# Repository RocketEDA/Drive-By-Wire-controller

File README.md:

# DBW-controller

DISCLAIMER: Please read the LICENSE file. Electronic throttle body control is not for the faint of heart. It can result in injury or death of road users. Test, verify, and test again before using on a road with other people. Understand the software and hardware, how they interact, apply good engineering principles and common sense.
As stated in the LICENSE file, by using this project in any way, you agree to take on full responsibilities to damages caused by this project.

Drive by wire controller, maps throttle to throttle body 1:1 with idle control

For my application I used a Chrysler/mercedes 75mm throttle body with a corvette c6 throttle pedal.
P/N 0280750570
P/N 25835421

SOFTWARE:
Code is fully commented.

Schematic description:
arduino nano handles all the code and control. 
D2 has an input for switch SW2, signaling to enter setup mode
A6 has a potentiometer, handling idle control.
For servo drive a BTS7960 module from amazon is used.

PCA9685 is used for better PWM control. PWM0 and PWM is used for the BTS, the rest are open

Optionally popuplate R11 and R12. The chrylser TB used a HAR3726 magnetic sensor which specifies for a 10k RL

Assembly notes:
The capacitor and terminal blocks will need to moved to the other side on the BTS7960 to clear. I took this opportunity to upsize the capacitor as well, not sure if there's any appreciatable benefit.

J2 and J4 connect to the TB TPS and e-pedal TPS.
Both e-pedal TPS's are positive direction, aka voltage increases as TPS approaches "open"
TB TPS has one signal inverted. To change this the calculation can be modified:

Upon first run, the "setup" switch should be set. Plugin a USB and set baud to 115200 to follow setup instructions. The potentiometer sets idle (minimum) throttle position. The equation is as follows. Insert a DMM probe between GND and IDLE to measure the pot's voltage. The idle % equation is: Idle position % = (IDLE voltage / 5) * (MAX_IDLE_TB_OPEN / 1023) * 100

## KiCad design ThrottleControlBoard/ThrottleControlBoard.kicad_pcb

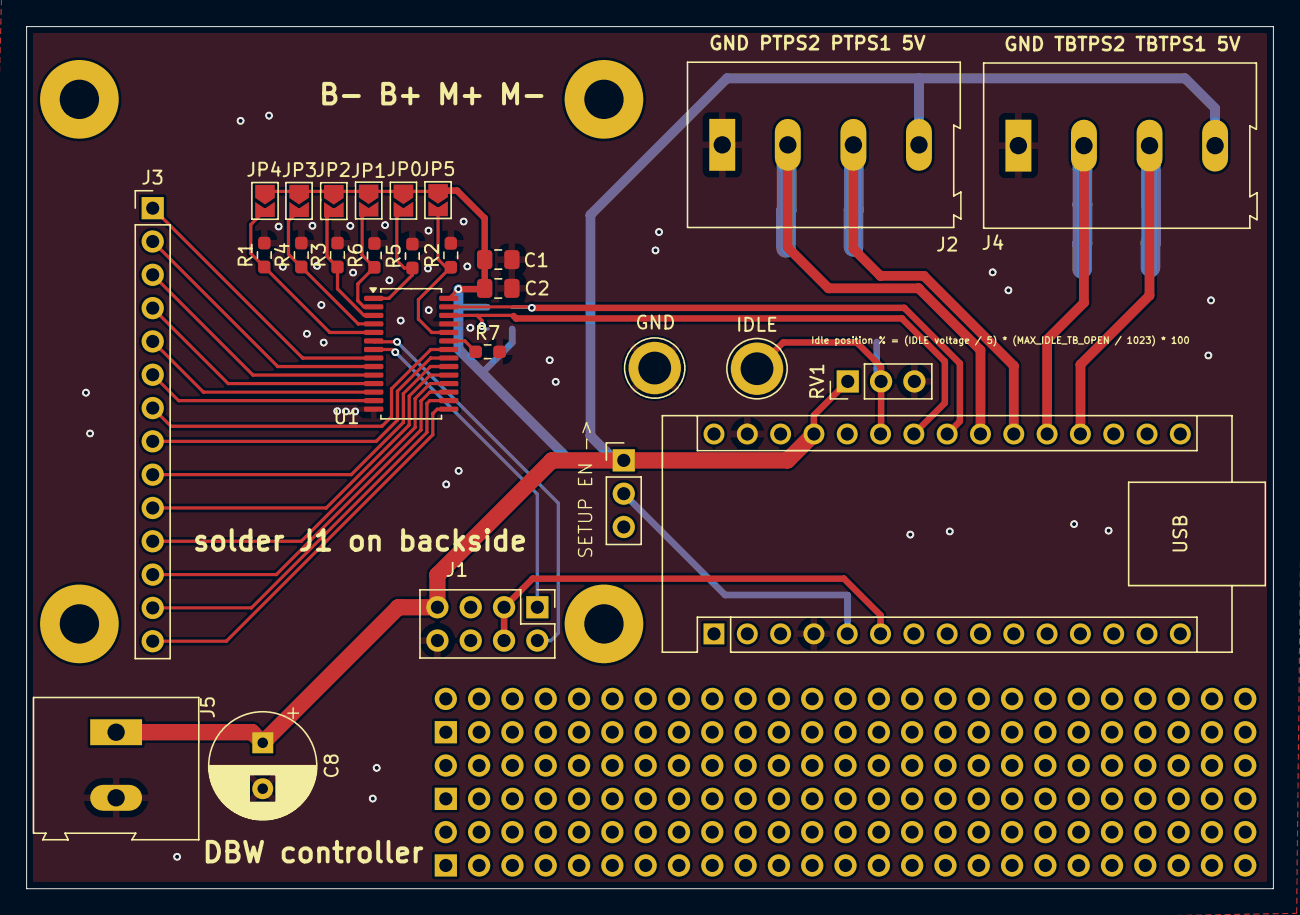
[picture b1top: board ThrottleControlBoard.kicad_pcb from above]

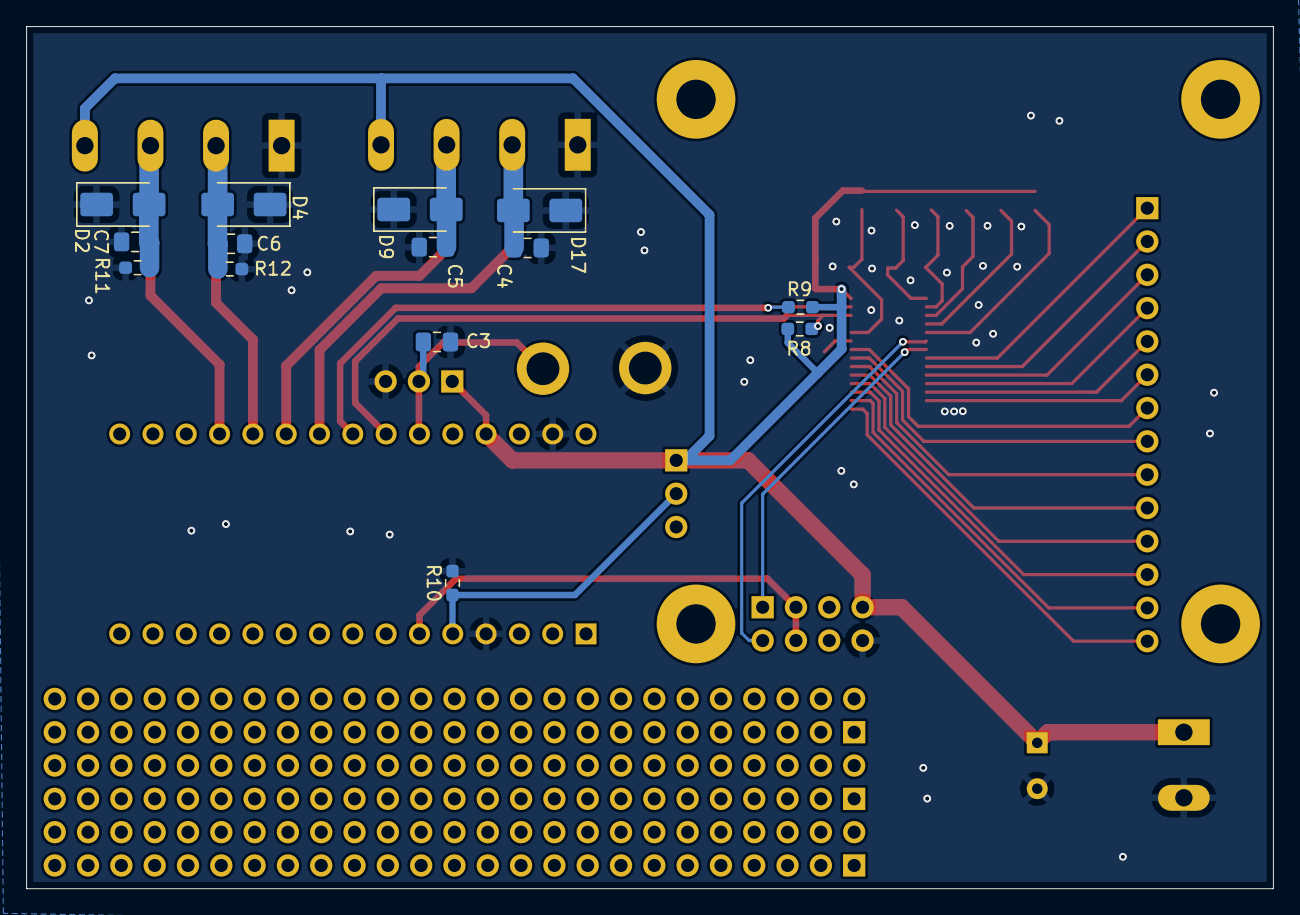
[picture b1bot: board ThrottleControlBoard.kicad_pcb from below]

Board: 2 copper layers, 95.1 x 65.7 mm, 44 parts (14 on the bottom side), 34 nets.

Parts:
A1: Arduino_Nano_Every; Arduino_Nano
C1: 10uF; C_0805_2012Metric_Pad1.18x1.45mm_HandSolder
C2: 100nF; C_0805_2012Metric_Pad1.18x1.45mm_HandSolder
C3, C4, C5, C6, C7: 1nF; C_0805_2012Metric_Pad1.18x1.45mm_HandSolder
C8: 470uF; CP_Radial_D8.0mm_P3.50mm
D2, D4, D9, D17: SMAJ5.0CA; D_SMA
J1: BTS7960 module; PinHeader_2x04_P2.54mm_Vertical
J2: e-Throttle; TerminalBlock_Altech_AK300-4_P5.00mm
J3: Conn_01x14; PinHeader_1x14_P2.54mm_Vertical
J4: TB TPS; TerminalBlock_Altech_AK300-4_P5.00mm
J5: 5V; TerminalBlock_Altech_AK300-2_P5.00mm
J6, J7, J10: Conn_02x25_Odd_Even; PinHeader_2x25_P2.54mm_Vertical
JP0, JP1, JP2, JP3, JP4, JP5: SolderJumper_2_Open; SolderJumper-2_P1.3mm_Open_TrianglePad1.0x1.5mm
R1, R2, R3, R4, R5, R6, R7, R8, R9, R10, R11, R12: 10k; R_0603_1608Metric_Pad0.98x0.95mm_HandSolder
RV1: R_Potentiometer_Trim; PinHeader_1x03_P2.54mm_Vertical
SW2: SW_SPDT; PinHeader_1x03_P2.54mm_Vertical
TP1: IDLE; TestPoint_Loop_D3.80mm_Drill2.5mm
TP2: GND; TestPoint_Loop_D3.80mm_Drill2.5mm
U1: PCA9685PW; TSSOP-28_4.4x9.7mm_P0.65mm

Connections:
GND: A1.4 (GND), A1.29 (GND), C1.2, C2.2, C3.2, C4.2, C5.2, C6.2, C7.2, C8.2, D2.1 (A1), D4.1 (A1), D9.1 (A1), D17.1 (A1), J1.8, J2.1, J4.1, J5.2, R1.2, R2.2, R3.2, R4.2, R5.2, R6.2, R7.2, R10.2, R11.2, R12.2, RV1.3, TP2.1, U1.14 (VSS), U1.25 (EXTCLK)
L_EN: A1.6 (D3), J1.3, J1.4
L_PWM: J1.2, U1.6 (LED0)
unnamed: A1.25 (A6), C3.1, RV1.2, TP1.1
unnamed: A1.5 (D2), R10.1, SW2.2 (B)
unnamed: JP0.2 (B), R5.1, U1.1 (A0)
unnamed: JP1.2 (B), R6.1, U1.2 (A1)
unnamed: JP2.2 (B), R3.1, U1.3 (A2)
unnamed: JP3.2 (B), R4.1, U1.4 (A3)
unnamed: JP4.2 (B), R1.1, U1.5 (A4)
unnamed: JP5.2 (B), R2.1, U1.24 (A5)
unnamed: R7.1, U1.23 (~OE)
PTPS1: A1.21 (A2), C5.1, D9.2 (A2), J2.3
PTPS2: A1.22 (A3), C4.1, D17.2 (A2), J2.2
PWM1: J1.1, U1.7 (LED1)
PWM2: J3.1, U1.8 (LED2)
PWM3: J3.2, U1.9 (LED3)
PWM4: J3.3, U1.10 (LED4)
PWM5: J3.4, U1.11 (LED5)
PWM6: J3.5, U1.12 (LED6)
PWM7: J3.6, U1.13 (LED7)
PWM8: J3.14, U1.15 (LED8)
PWM9: J3.13, U1.16 (LED9)
PWM10: J3.12, U1.17 (LED10)
PWM11: J3.11, U1.18 (LED11)
PWM12: J3.10, U1.19 (LED12)
PWM13: J3.9, U1.20 (LED13)
PWM14: J3.8, U1.21 (LED14)
PWM15: J3.7, U1.22 (LED15)
SCL: A1.24 (SCL/A5), R8.2, U1.26 (SCL)
SDA: A1.23 (SDA/A4), R9.2, U1.27 (SDA)
TBTPS1: A1.19 (A0), C7.1, D2.2 (A2), J4.3, R11.1
TBTPS2: A1.20 (A1), C6.1, D4.2 (A2), J4.2, R12.1
VDD: A1.27 (+5V), C1.1, C2.1, C8.1, J1.7, J2.4, J4.4, J5.1, JP0.1 (A), JP1.1 (A), JP2.1 (A), JP3.1 (A), JP4.1 (A), JP5.1 (A), R8.1, R9.1, RV1.1, SW2.1 (A), U1.28 (VDD)

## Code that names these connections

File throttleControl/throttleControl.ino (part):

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//PCA9685 pins
#define LPWM_pin 0      //PWM pin on PCA9685
#define RPWM_pin 1      //PWM pin on PCA9685
#define EN_pin 3        //R_EN/L_EN tied together
//#define RIS_pin         //overcurrent alarm right
//#define LIS_pin         //overcurrent alarm right

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#define PTPS_var 300

//throttle body pot pins
#define TBTPS1_pin A0
#define TBTPS2_pin A1

//e-pedal pot pins
#define PTPS1_pin A2
#define PTPS2_pin A3

//min throttle idle pot pin
#define IDLE_POT_pin A6
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*/
void readTBTPS()
{
  tbtps1_val = analogRead(TBTPS1_pin);
  tbtps2_val = analogRead(TBTPS2_pin);
}

/*
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void readPTPS()
{
  //invert if pins are inversed
  ptps1_val = analogRead(PTPS2_pin);
  ptps2_val = analogRead(PTPS1_pin);
}
/*
   calculateTBTPS
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
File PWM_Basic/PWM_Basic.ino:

/****************************************************************************************************************************
  PWM_Basic.ino

  For AVR-based boards  (UNO, Nano, Mega, 32U4, 16U4, etc. )
  Written by Khoi Hoang

  Built by Khoi Hoang https://github.com/khoih-prog/AVR_PWM
  Licensed under MIT license

  This is pure hardware-based PWM
*****************************************************************************************************************************/
/******************************************************************************************************************************
  // For UNO / Nano
  Timer0 ( 8-bit) used by delay(), millis() and micros(), and PWM generation on pins 5 (6 not usable)
  Timer1 (16-bit) used by the Servo.h library and PWM generation on pins 9 and 10
  Timer2 ( 8-bit) used by Tone() and PWM generation on pins 3 and 11
  // For Mega
  Timer0 ( 8-bit) used by delay(), millis() and micros(), and PWM generation on pins 4 (13 not usable)
  Timer1 (16-bit) used by the Servo.h library and PWM generation on pins 11, 12
  Timer2 ( 8-bit) used by Tone() and PWM generation on pins 9 and 10
  Timer3 (16-bit) used by PWM generation on pins  2,  3 and  5
  Timer4 (16-bit) used by PWM generation on pins  6,  7 and  8
  Timer5 (16-bit) used by PWM generation on pins 44, 45 and 46

  ////////////////////////////////////////////
  // For Mega (2, 3, 4, 5, 6, 7, 8, 9, 10, 11, 12, 13, 44, 45, 46)
  Pin  2 => TIMER3B   // PE 4 ** 2  ** PWM2
  Pin  3 => TIMER3C   // PE 5 ** 3  ** PWM3
  Pin  4 => TIMER0B   // PG 5 ** 4  ** PWM4
  Pin  5 => TIMER3A   // PE 3 ** 5  ** PWM5
  Pin  6 => TIMER4A   // PH 3 ** 6  ** PWM6
  Pin  7 => TIMER4B   // PH 4 ** 7  ** PWM7
  Pin  8 => TIMER4C   // PH 5 ** 8  ** PWM8
  Pin  9 => TIMER2B   // PH 6 ** 9  ** PWM9
  Pin 10 => TIMER2A   // PB 4 ** 10 ** PWM10
  Pin 11 => TIMER1A   // PB 5 ** 11 ** PWM11
  Pin 12 => TIMER1B   // PB 6 ** 12 ** PWM12
  Pin 13 => TIMER0A   // PB 7 ** 13 ** PWM13
  Pin 44 => TIMER5C   // PL 5 ** 44 ** D44
  Pin 45 => TIMER5B   // PL 4 ** 45 ** D45
  Pin 46 => TIMER5A   // PL 3 ** 46 ** D46
  ////////////////////////////////////////////
  // For 32u4 (3, 5, 6, 9, 10, 11, 13)
  Pin  3 => TIMER0B
  Pin  5 => TIMER3A
  Pin  6 => TIMER4D
  Pin  9 => TIMER1A
  Pin 10 => TIMER1B
  Pin 11 => TIMER0A
  Pin 13 => TIMER4A
  ////////////////////////////////////////////
  // For UNO, Nano (3, 5, 6, 9, 10, 11)
  Pin  3 => TIMER2B,
  Pin  5 => TIMER0B
  Pin  6 => TIMER0A
  Pin  9 => TIMER1A
  Pin 10 => TIMER1B
  Pin 11 => TIMER2(A)
******************************************************************************************************************************/

#define _PWM_LOGLEVEL_       4

#include "AVR_PWM.h"

  // Pins tested OK on Nano / UNO
  //#define pinToUse      9            // Timer1A on UNO, Nano, etc
  //#define pinToUse     10            // Timer1B on UNO, Nano, etc
  //#define pinToUse      5               // Timer0B on UNO, Nano, e
#define pinToUse       3            // Timer2B on UNO, Nano, etc

//creates pwm instance
AVR_PWM* PWM_Instance;

float frequency;
float dutyCycle;

void setup()
{
  Serial.print(F("\nStarting PWM_Basic on "));
  Serial.println(BOARD_NAME);
  Serial.println(AVR_PWM_VERSION);

  //assigns PWM frequency of 20 KHz and a duty cycle of 0%
  PWM_Instance = new AVR_PWM(pinToUse, 20000, 0);
}

void loop()
{
  //delay(10000);
  frequency = 500;    //20000;
  dutyCycle = 20;     //90;

  PWM_Instance->setPWM(pinToUse, frequency, dutyCycle);

  delay(10000);
  dutyCycle = 300;

  PWM_Instance->setPWM(pinToUse, frequency, dutyCycle);

  delay(10000);
}

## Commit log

2024-04-14 initial commit
    8 bit servo control working with l298
2024-04-18 working code with BTS
    test showed very good results
2024-04-22 code implementations completed
    EEPROM save throttle position state, save idle based on pot
    enter setup option upon startup
2024-04-23 PCB done
2024-04-23 DRC and vias fixed
2024-04-23 gerbers exported
2024-04-23 Create LICENSE
2024-04-26 idle position not setting issue fixed
2024-09-08 more lenient ptps_var
